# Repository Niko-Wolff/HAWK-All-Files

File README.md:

# HAWK-Flight-Computer
This includes all manufacturing files for the HAWK flight computer, as well as the purchasing links.

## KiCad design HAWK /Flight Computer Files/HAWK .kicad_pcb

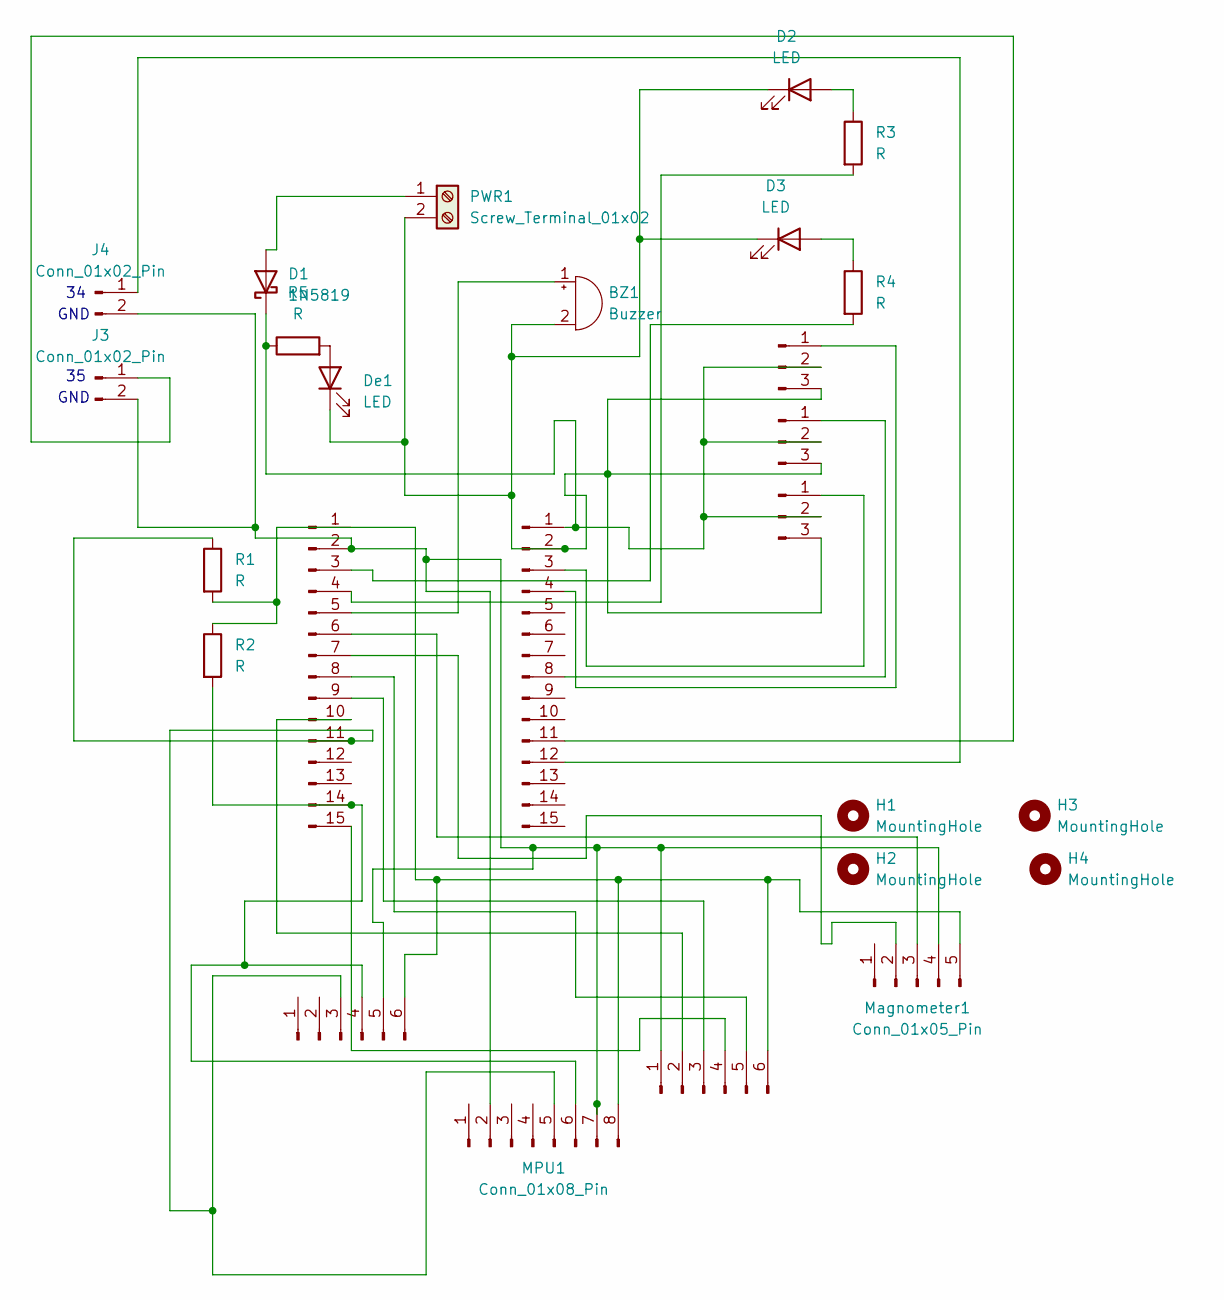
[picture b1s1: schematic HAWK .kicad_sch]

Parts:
BMP1: Conn_01x06_Pin; PinHeader_1x06_P2.54mm_Vertical
BZ1: Buzzer; MagneticBuzzer_PUI_AT-0927-TT-6-R
D1: 1N5819; D_DO-41_SOD81_P10.16mm_Horizontal
D2, D3: LED; LED_D5.0mm
De1: LED; LED_D5.0mm
H1, H2, H3, H4: MountingHole; MountingHole_3.2mm_M3
J1, J2: Conn_01x15_Pin; PinHeader_1x15_P2.54mm_Vertical
J3, J4: Conn_01x02_Pin; PinHeader_1x02_P2.54mm_Vertical
J8, J9, J10: Conn_01x03_Pin; PinHeader_1x03_P2.54mm_Vertical
MPU1: Conn_01x08_Pin; PinHeader_1x08_P2.54mm_Vertical
Magnometer1: Conn_01x05_Pin; PinHeader_1x05_P2.54mm_Vertical
PWR1: Screw_Terminal_01x02; TerminalBlock_Phoenix_MPT-0,5-2-2.54_1x02_P2.54mm_Horizontal
R1, R2, R3, R4, R5: R; R_Axial_DIN0207_L6.3mm_D2.5mm_P10.16mm_Horizontal
SD1: Conn_01x06_Pin; PinHeader_1x06_P2.54mm_Vertical

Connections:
unnamed: BMP1.3, J1.11, MPU1.5, R1.1
unnamed: BMP1.4, J1.14, MPU1.6, R2.2
unnamed: BMP1.5, J1.2, J3.2, J4.2, MPU1.2, MPU1.7, Magnometer1.4, SD1.1
unnamed: BMP1.6, MPU1.8, Magnometer1.5, R1.2, R2.1, SD1.6
unnamed: BZ1.1 (+), J1.5
unnamed: BZ1.2 (-), D2.1 (K), D3.1 (K), De1.1 (K), J2.2, J8.3, J9.3, J10.3, PWR1.2
unnamed: D1.2 (A), PWR1.1
unnamed: D1.1 (K), J2.1, J8.2, J9.2, J10.2, R5.1
unnamed: D2.2 (A), R3.1
unnamed: D3.2 (A), R4.1
unnamed: De1.2 (A), R5.2
unnamed: J1.3, R4.2
unnamed: J1.4, R3.2
unnamed: J1.6, Magnometer1.3
unnamed: J1.7, Magnometer1.2
unnamed: J1.8, SD1.5
unnamed: J1.9, SD1.3
unnamed: J1.10, SD1.2
unnamed: J1.15, SD1.4
unnamed: J2.4, J8.1
unnamed: J2.8, J9.1
unnamed: J2.11, J3.1
unnamed: J2.12, J4.1
unnamed: J2.3, J10.1

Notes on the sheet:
GND

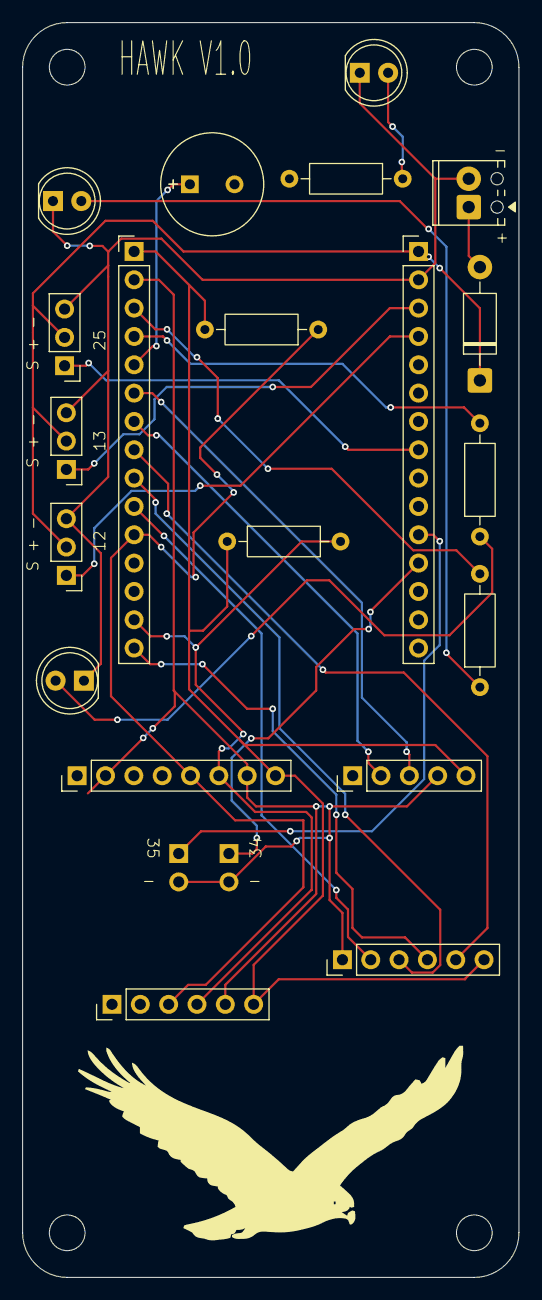
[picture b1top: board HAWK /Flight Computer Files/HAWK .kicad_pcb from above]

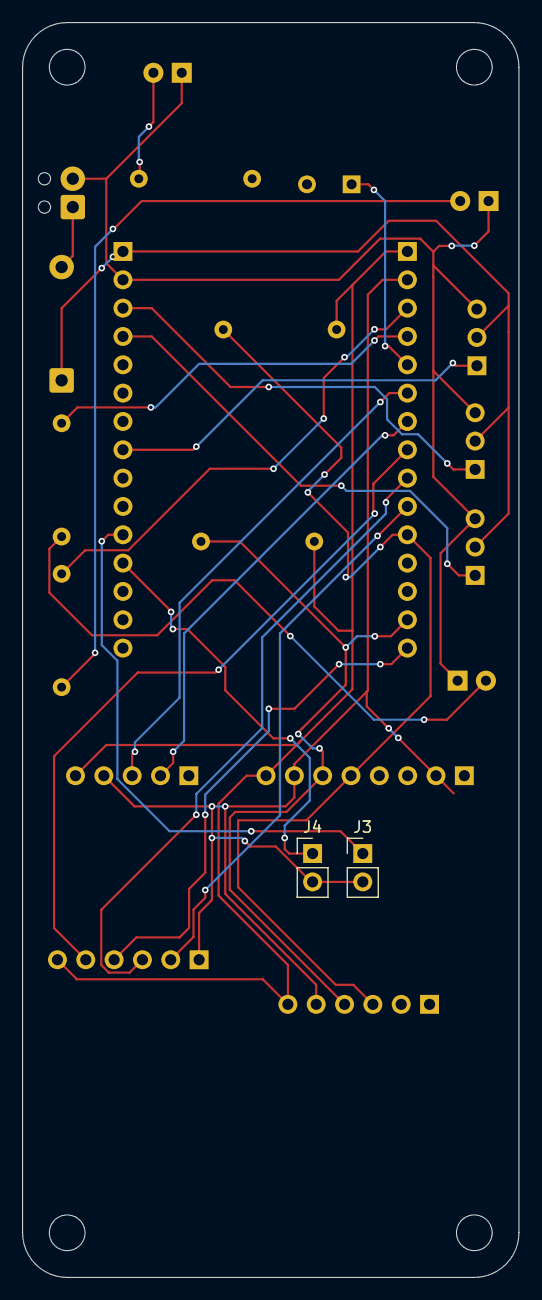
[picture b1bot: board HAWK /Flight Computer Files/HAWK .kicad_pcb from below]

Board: 2 copper layers, 44.5 x 112.5 mm, 26 parts (2 on the bottom side), 24 nets.

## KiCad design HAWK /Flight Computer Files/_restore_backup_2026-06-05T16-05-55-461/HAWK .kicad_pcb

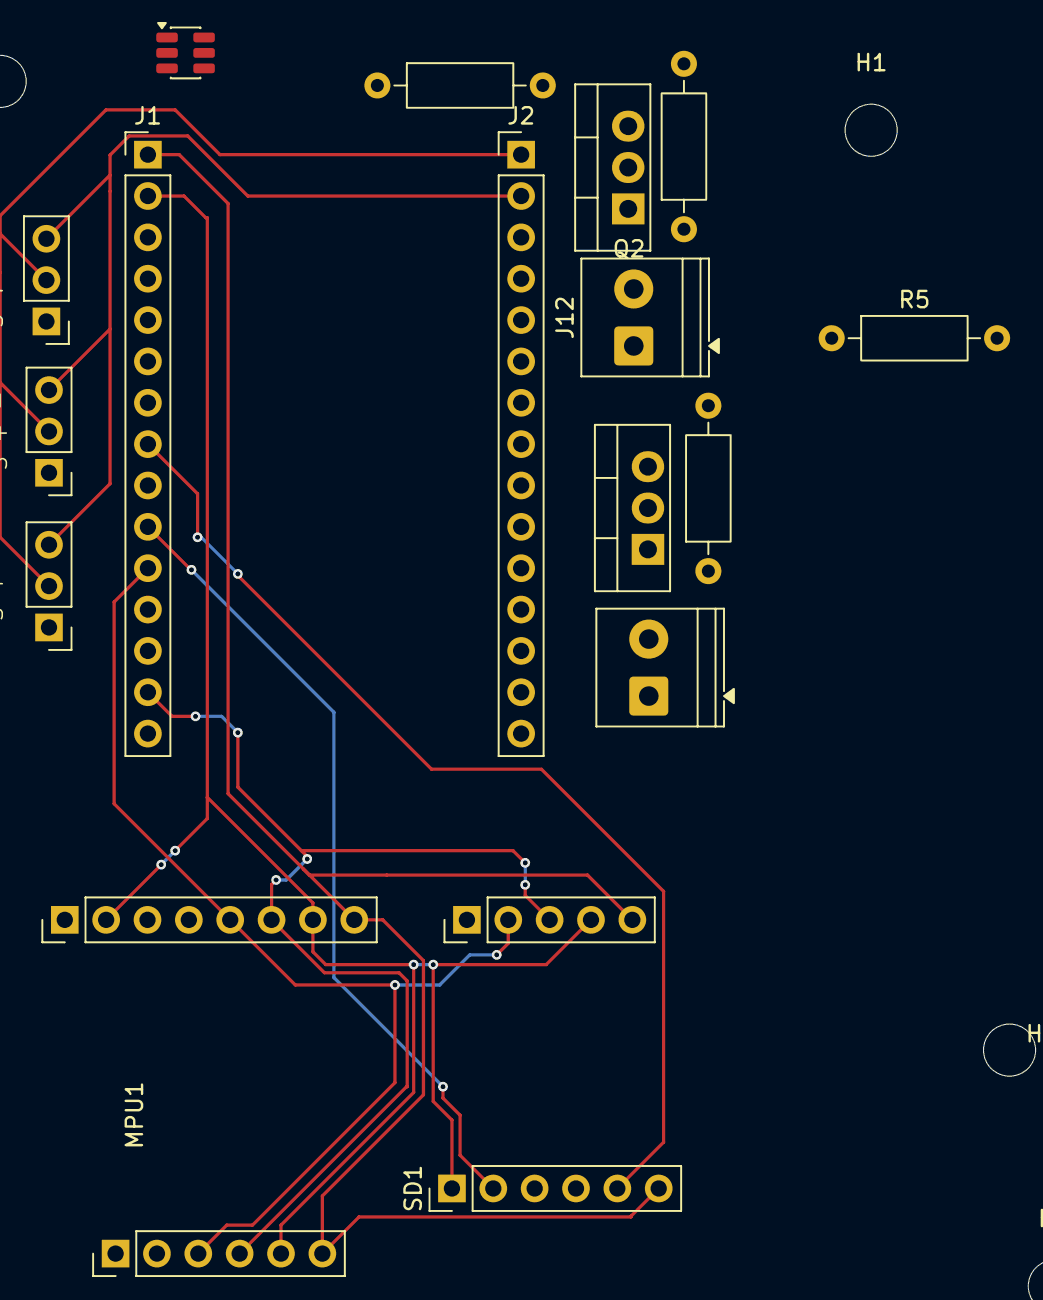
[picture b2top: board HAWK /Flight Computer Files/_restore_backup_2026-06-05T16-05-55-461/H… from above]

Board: 2 copper layers, 22 parts (0 on the bottom side), 12 nets.

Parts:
BMP1: Conn_01x06_Pin; PinHeader_1x06_P2.54mm_Vertical
H1, H2, H3, H4: MountingHole; MountingHole_3.2mm_M3
J1, J2: Conn_01x15_Pin; PinHeader_1x15_P2.54mm_Vertical
J8, J9, J10: Conn_01x03_Pin; PinHeader_1x03_P2.54mm_Vertical
J11, J12: Screw_Terminal_01x02; TerminalBlock_Phoenix_PT-1,5-2-3.5-H_1x02_P3.50mm_Horizontal
MPU1: Conn_01x08_Pin; PinHeader_1x08_P2.54mm_Vertical
Magnometer1: Conn_01x05_Pin; PinHeader_1x05_P2.54mm_Vertical
Q1, Q2: IRLZ44N; TO-220-3_Vertical
R3, R4: 10k; R_Axial_DIN0207_L6.3mm_D2.5mm_P10.16mm_Horizontal
R5, R6: 330; R_Axial_DIN0207_L6.3mm_D2.5mm_P10.16mm_Horizontal
SD1: Conn_01x06_Pin; PinHeader_1x06_P2.54mm_Vertical
U1: MT3608; SOT-23-6

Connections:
unnamed: BMP1.3, J1.11, MPU1.5, Magnometer1.2
unnamed: BMP1.4, J1.14, MPU1.6, Magnometer1.3
unnamed: BMP1.5, J1.2, MPU1.2, MPU1.7, Magnometer1.4, SD1.1
unnamed: BMP1.6, J1.1, MPU1.8, Magnometer1.5, SD1.6
unnamed: J1.8, SD1.5
unnamed: J1.9, SD1.3
unnamed: J1.10, SD1.2
unnamed: J1.15, SD1.4
unnamed: J2.1, J8.2, J9.2, J10.2
unnamed: J2.2, J8.3, J9.3, J10.3, Q1.3 (S), Q2.3 (S), R3.2, R4.2
unnamed: Q1.1 (G), R4.1, R5.2
unnamed: Q2.1 (G), R3.1, R6.2
